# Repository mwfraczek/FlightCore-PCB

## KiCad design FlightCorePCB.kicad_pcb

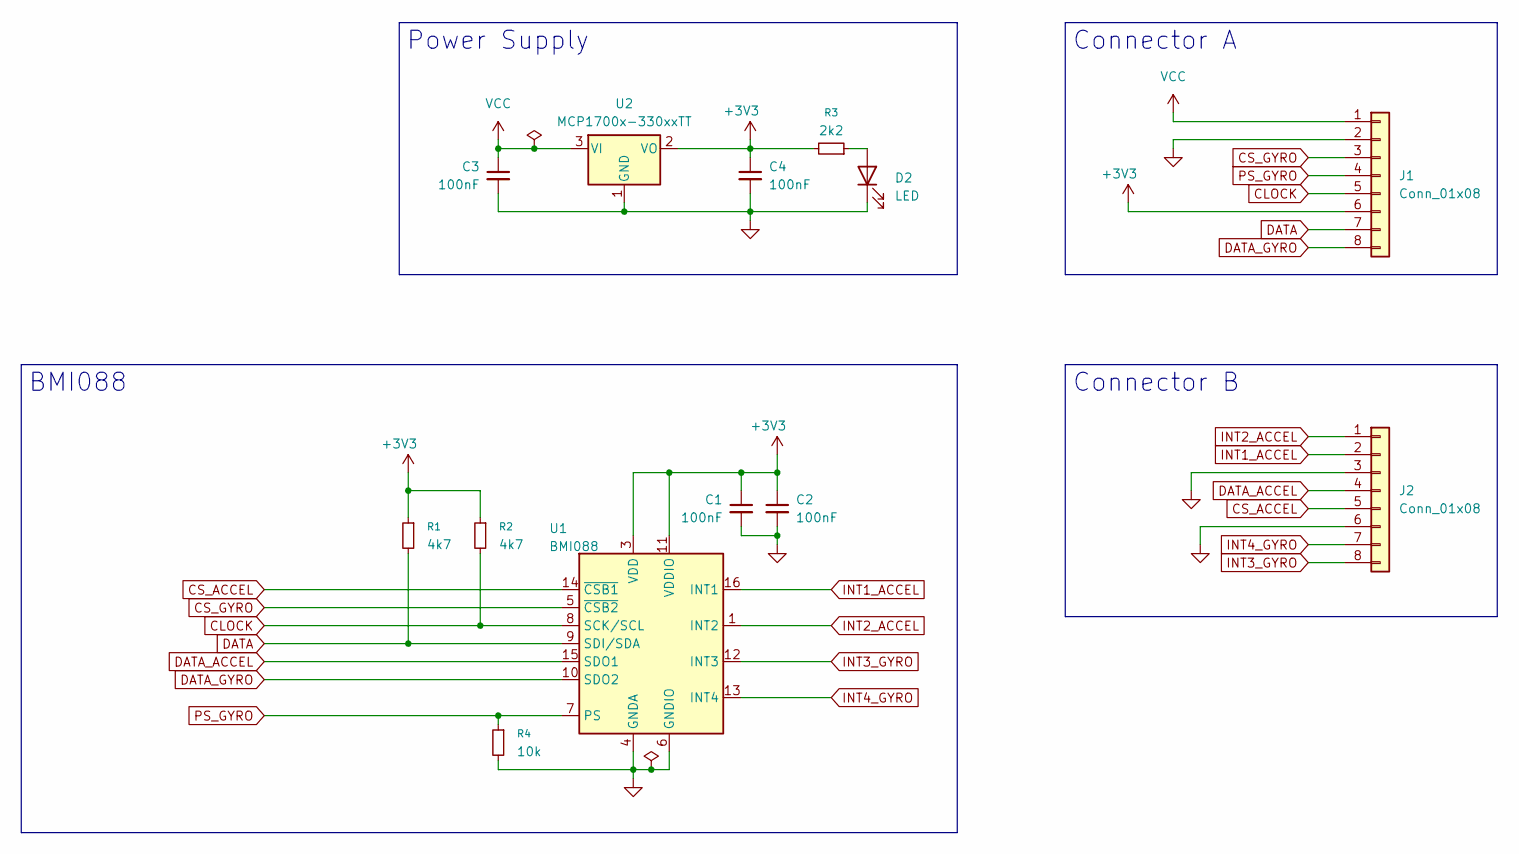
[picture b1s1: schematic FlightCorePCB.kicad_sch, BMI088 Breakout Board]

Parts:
C1, C2: 100nF; C_0402_1005Metric
C3, C4: 100nF; C_0603_1608Metric
D2: LED; LED_0603_1608Metric
J1, J2: Conn_01x08; PinHeader_1x08_P2.54mm_Vertical
R1, R2: 4k7; R_0603_1608Metric
R3: 2k2; R_0603_1608Metric
R4: 10k; R_0603_1608Metric
U1: BMI088; Bosch_LGA-16_4.5x3mm_P0.5mm_LayoutBorder7x1y_ClockwisePinNu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
U2: MCP1700x-330xxTT; SOT-23

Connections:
+3V3: C1.1, C2.1, C4.1, J1.6, R1.1, R2.1, R3.2, U1.3 (VDD), U1.11 (VDDIO), U2.2 (VO)
CLOCK: J1.5, R2.2, U1.8 (SCK/SCL)
CS_ACCEL: J2.5, U1.14 (~CSB1)
CS_GYRO: J1.3, U1.5 (~CSB2)
DATA: J1.7, R1.2, U1.9 (SDI/SDA)
DATA_ACCEL: J2.4, U1.15 (SDO1)
DATA_GYRO: J1.8, U1.10 (SDO2)
GND: C1.2, C2.2, C3.2, C4.2, D2.1 (K), J1.2, J2.3, J2.6, R4.2, U1.2 (GNDA), U1.4 (GNDA), U1.6 (GNDIO), U2.1 (GND)
INT1_ACCEL: J2.2, U1.16 (INT1)
INT2_ACCEL: J2.1, U1.1 (INT2)
INT3_GYRO: J2.8, U1.12 (INT3)
INT4_GYRO: J2.7, U1.13 (INT4)
unnamed: D2.2 (A), R3.1
PS_GYRO: J1.4, R4.1, U1.7 (PS)
VCC: C3.1, J1.1, U2.3 (VI)

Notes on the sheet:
Connector B
Connector A
Power Supply
BMI088

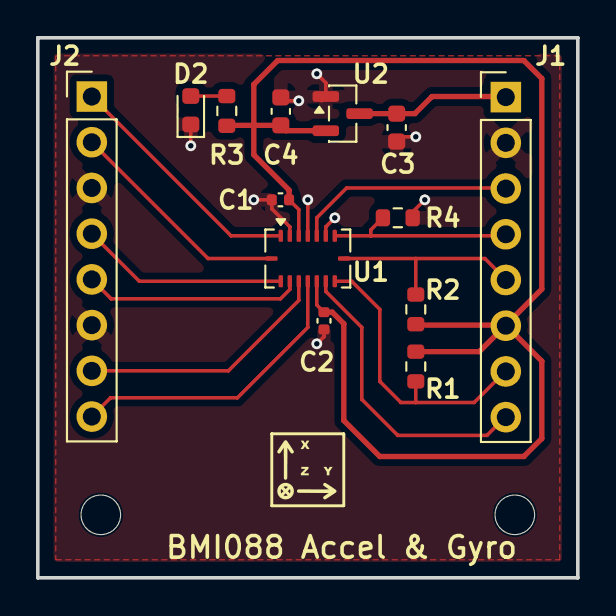
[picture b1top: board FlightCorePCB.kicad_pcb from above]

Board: 2 copper layers, 30.0 x 30.0 mm, 13 parts (0 on the bottom side), 15 nets.

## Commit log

2026-06-01 Add files via upload
    initial commit - schematic, layout, gerber, and drill files
